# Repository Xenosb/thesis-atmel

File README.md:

# thesis-atmel

## Libraries
Some of the symbols and footprints are from KiCad Library
```https://github.com/KiCad/kicad-library```

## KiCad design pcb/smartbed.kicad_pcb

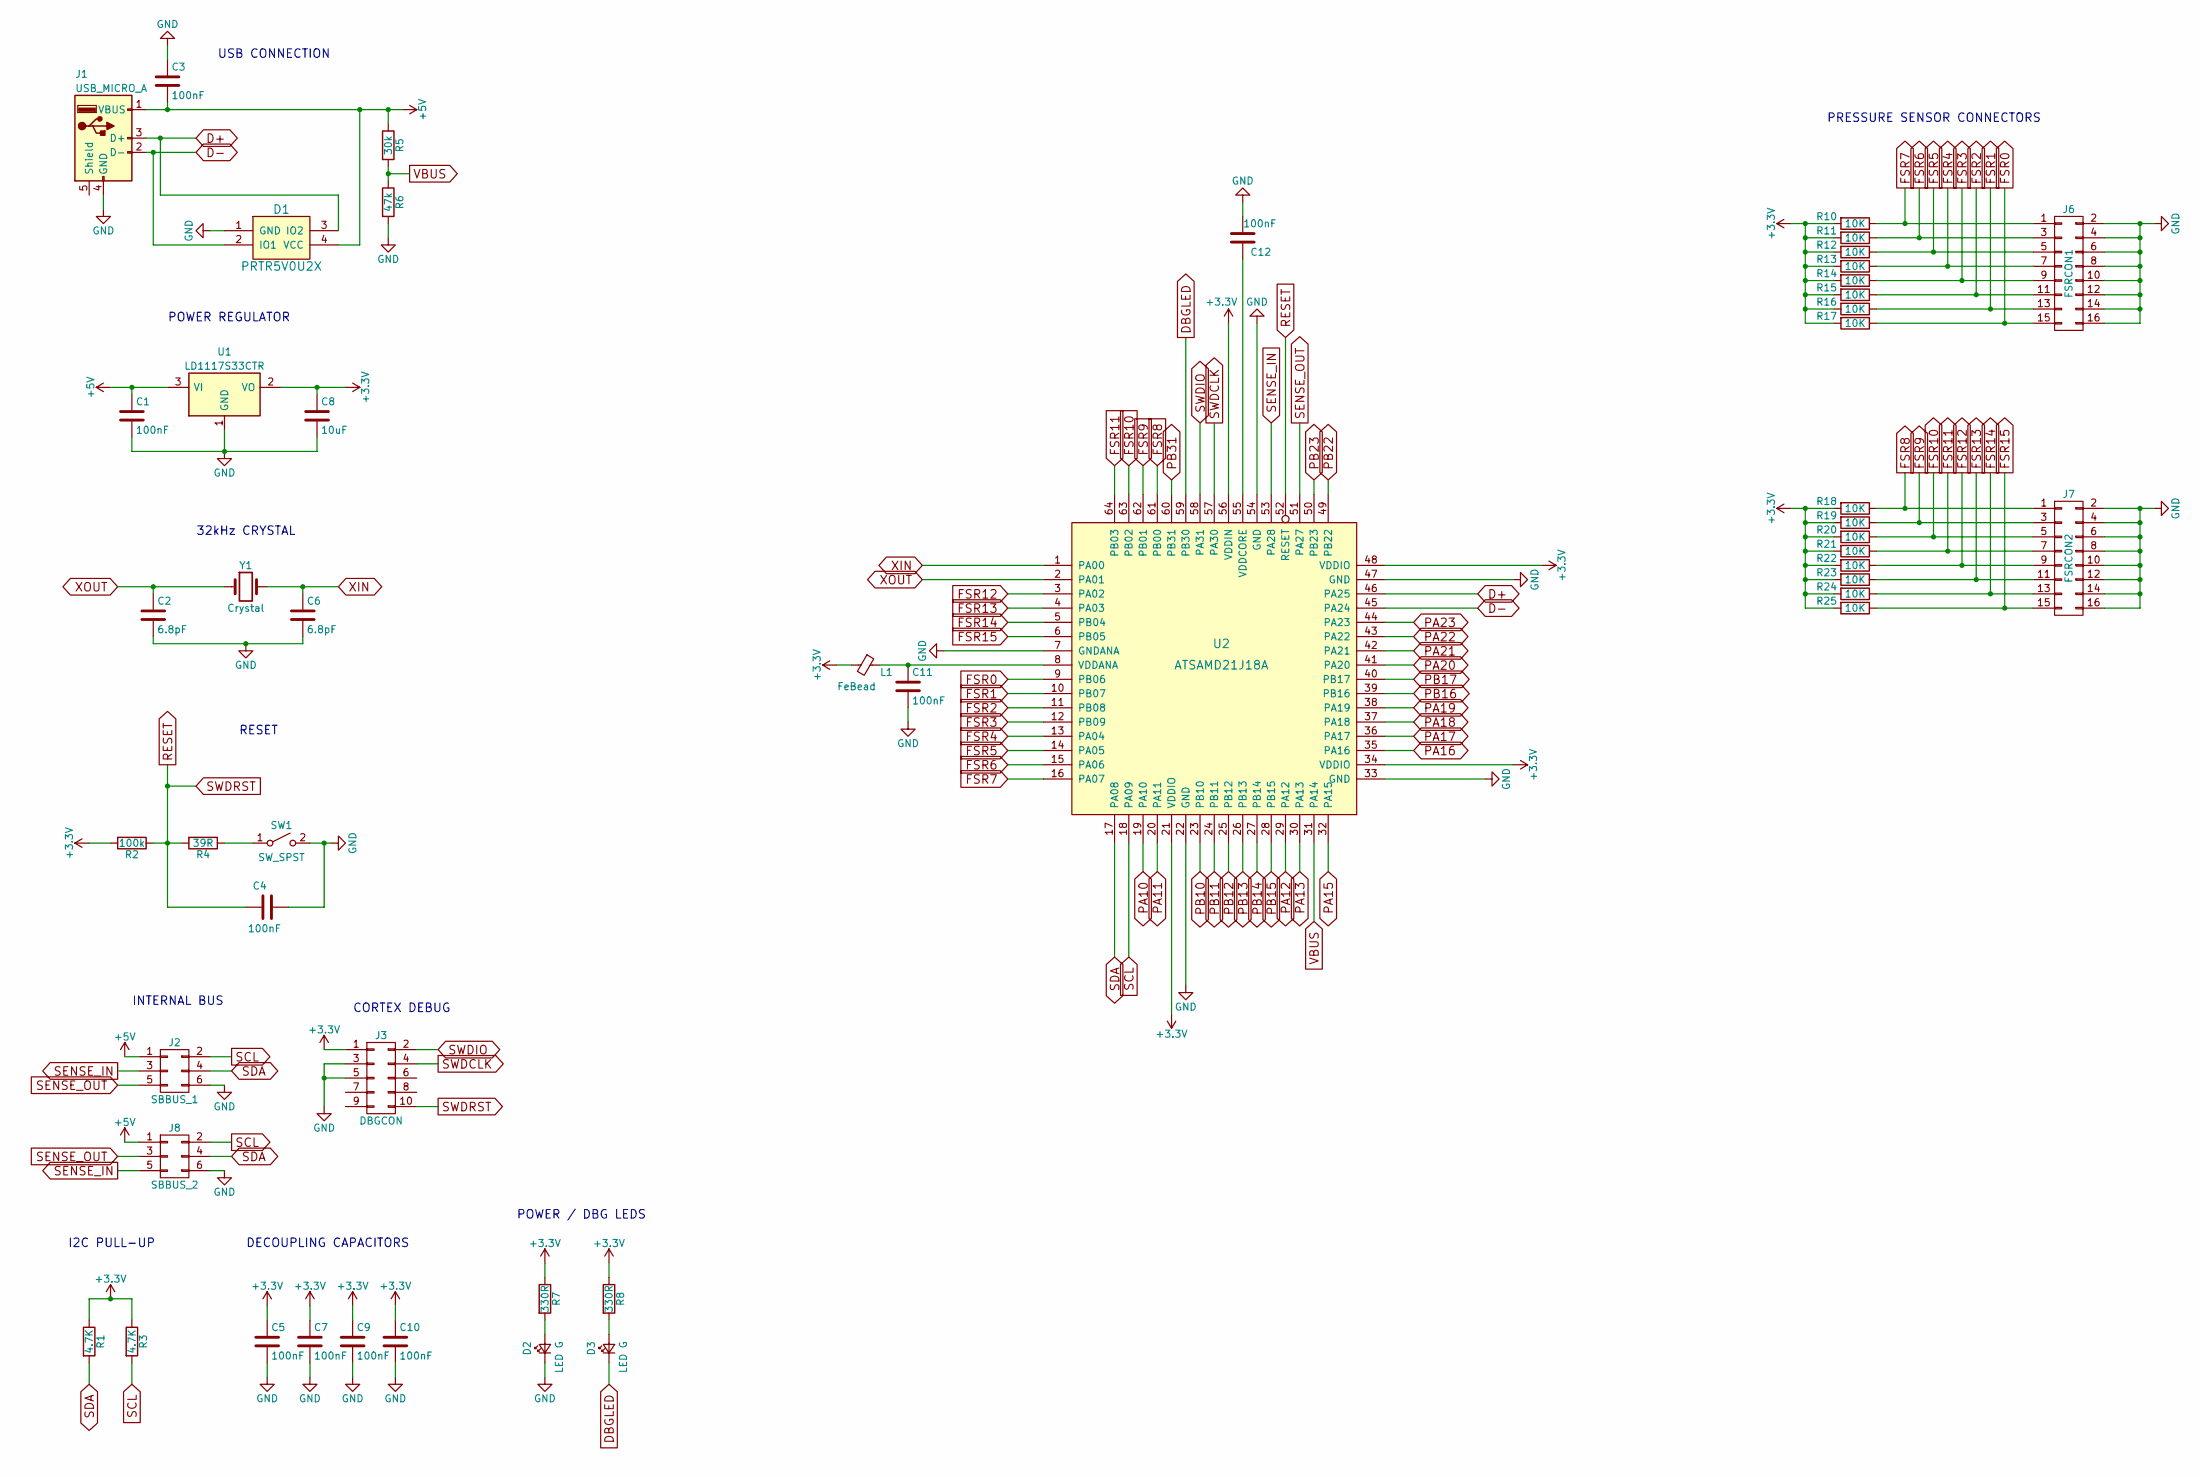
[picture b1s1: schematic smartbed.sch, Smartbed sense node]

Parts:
C1, C3, C4, C5, C7, C9, C10, C11, C12: 100nF; C_0603_HandSoldering
C2, C6: 6.8pF; C_0603_HandSoldering
C8: 10uF; C_0603_HandSoldering
D1: PRTR5V0U2X; SOT-143_Handsoldering
D2, D3: LED G; LED_0805
J1: USB_MICRO_A; USB_Micro-B
J2: SBBUS_1; IDC_Header_Straight_6pins
J3: DBGCON; IDC_Header_Straight_10pins
J6: FSRCON1; Pin_Header_Angled_2x08_Pitch2.54mm
J7: FSRCON2; Pin_Header_Angled_2x08_Pitch2.54mm
J8: SBBUS_2; IDC_Header_Straight_6pins
L1: FeBead; L_0603_HandSoldering
R1, R3: 4.7K; R_0805_HandSoldering
R2: 100k; R_0805_HandSoldering
R4: 39R; R_0805_HandSoldering
R5: 30k; R_0805_HandSoldering
R6: 47k; R_0805_HandSoldering
R7, R8: 330R; R_0805_HandSoldering
R10, R11, R12, R13, R14, R15, R16, R17, R18, R19, R20, R21, R22, R23, R24, R25: 10K; R_0805_HandSoldering
SW1: SW_SPST; SW_SPST_B3SL-1002P
U1: LD1117S33CTR; SOT-223
U2: ATSAMD21J18A; TQFP-64_10x10mm_Pitch0.5mm
Y1: Crystal; Crystal_Round_d3.0mm_Vertical

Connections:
+3V3: C5.1, C7.1, C8.1, C9.1, C10.1, J3.1, L1.2, R1.1, R2.2, R3.1, R7.1, R8.1, R10.2, R11.2, R12.2, R13.2, R14.2, R15.2, R16.2, R17.2, R18.2, R19.2, R20.2, R21.2, R22.2, R23.2, R24.2, R25.2, U1.2 (VO), U2.21 (VDDIO), U2.34 (VDDIO), U2.48 (VDDIO), U2.56 (VDDIN)
+5V: C1.1, C3.2, D1.4 (VCC), J1.1 (VBUS), J2.1, J8.1, R5.1, U1.3 (VI)
D+: D1.3 (IO2), J1.3 (D+), U2.46 (PA25)
D-: D1.2 (IO1), J1.2 (D-), U2.45 (PA24)
DBGLED: D3.1 (K), U2.59 (PB30)
FSR0: J6.15, R17.1, U2.9 (PB06)
FSR1: J6.13, R16.1, U2.10 (PB07)
FSR2: J6.11, R15.1, U2.11 (PB08)
FSR3: J6.9, R14.1, U2.12 (PB09)
FSR4: J6.7, R13.1, U2.13 (PA04)
FSR5: J6.5, R12.1, U2.14 (PA05)
FSR6: J6.3, R11.1, U2.15 (PA06)
FSR7: J6.1, R10.1, U2.16 (PA07)
FSR8: J7.1, R18.1, U2.61 (PB00)
FSR9: J7.3, R19.1, U2.62 (PB01)
FSR10: J7.5, R20.1, U2.63 (PB02)
FSR11: J7.7, R21.1, U2.64 (PB03)
FSR12: J7.9, R22.1, U2.3 (PA02)
FSR13: J7.11, R23.1, U2.4 (PA03)
FSR14: J7.13, R24.1, U2.5 (PB04)
FSR15: J7.15, R25.1, U2.6 (PB05)
GND: C1.2, C2.2, C3.1, C4.2, C5.2, C6.2, C7.2, C8.2, C9.2, C10.2, C11.2, C12.1, D1.1 (GND), D2.1 (K), J1.4 (GND), J2.6, J3.3, J3.5, J6.2, J6.4, J6.6, J6.8, J6.10, J6.12, J6.14, J6.16, J7.2, J7.4, J7.6, J7.8, J7.10, J7.12, J7.14, J7.16, J8.6, R6.2, SW1.2 (B), U1.1 (GND), U2.7 (GNDANA), U2.22 (GND), U2.33 (GND), U2.47 (GND), U2.54 (GND)
unnamed: C11.1, L1.1, U2.8 (VDDANA)
unnamed: C12.2, U2.55 (VDDCORE)
unnamed: D2.2 (A), R7.2
unnamed: D3.2 (A), R8.2
unnamed: R4.1, SW1.1 (A)
PA10: U2.19 (PA10)
PA11: U2.20 (PA11)
PA12: U2.29 (PA12)
PA13: U2.30 (PA13)
PA15: U2.32 (PA15)
PA16: U2.35 (PA16)
PA17: U2.36 (PA17)
PA18: U2.37 (PA18)
PA19: U2.38 (PA19)
PA20: U2.41 (PA20)
PA21: U2.42 (PA21)
PA22: U2.43 (PA22)
PA23: U2.44 (PA23)
PB10: U2.23 (PB10)
PB11: U2.24 (PB11)
PB12: U2.25 (PB12)
PB13: U2.26 (PB13)
PB14: U2.27 (PB14)
PB15: U2.28 (PB15)
PB16: U2.39 (PB16)
PB17: U2.40 (PB17)
PB22: U2.49 (PB22)
PB23: U2.50 (PB23)
PB31: U2.60 (PB31)
RESET: C4.1, J3.10, R2.1, R4.2, U2.52 (RESET)
SCL: J2.2, J8.2, R3.2, U2.18 (PA09)
SDA: J2.4, J8.4, R1.2, U2.17 (PA08)
SENSE_IN: J2.3, J8.5, U2.53 (PA28)
SENSE_OUT: J2.5, J8.3, U2.51 (PA27)
SWDCLK: J3.4, U2.57 (PA30)
SWDIO: J3.2, U2.58 (PA31)
VBUS: R5.2, R6.1, U2.31 (PA14)
XIN: C6.1, U2.1 (PA00), Y1.2
XOUT: C2.1, U2.2 (PA01), Y1.1

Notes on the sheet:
USB CONNECTION
INTERNAL BUS
POWER REGULATOR
32kHz CRYSTAL
RESET
I2C PULL-UP
CORTEX DEBUG
DECOUPLING CAPACITORS
POWER / DBG LEDS
PRESSURE SENSOR CONNECTORS

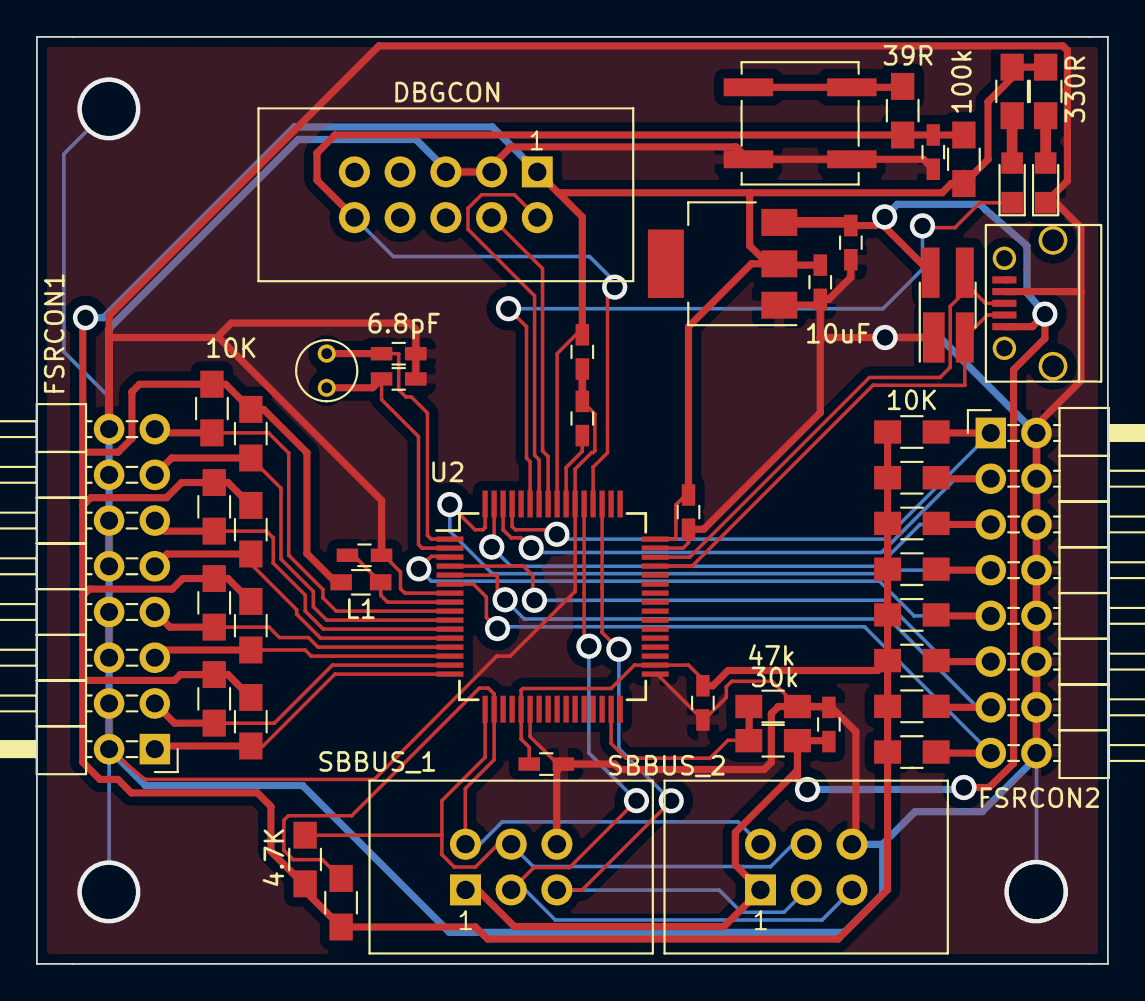
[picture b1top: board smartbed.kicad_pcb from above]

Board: 2 copper layers, 59.5 x 51.5 mm, 50 parts (0 on the bottom side), 37 nets.

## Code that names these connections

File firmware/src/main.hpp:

#define HW_VER 1
#define SW_VER 1

#include "mbed.h"
#include "Smartbed.hpp"

#define I2C_FREQ 100000
#define MAX_I2C_DATA_SIZE 100

#define EDISON_ADR 0x0a
#define NODE_ADR 0x10

#define I2C_SDA_PIN PA08
#define I2C_SCL_PIN PA09
#define LED_PIN PB30
#define SENSE_IN_PIN PA28
#define SENSE_OUT_PIN PA27

#define SENSOR_NUMBER 16

I2C_RESULT i2c_slave_worker(I2CSlave slave);
void process_i2c_call(I2C_RESULT i2c_data);
void process_read(I2C_RESULT i2c_data);
void process_write(I2C_RESULT i2c_data);
void process_broadcast(I2C_RESULT i2c_data);
void update_all_sensors();
int main();

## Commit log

2017-06-08 New gitiginre
2017-06-08 Added SAMD21 to library
2017-06-09 Added power supply, USB, internal bus
2017-06-09 Added I2C pull ups, reset button, xtal
2017-06-11 Added debug connector and capacitors
2017-06-11 Added FSR connectors
2017-06-11 Assigned footprints, started PCB
2017-06-12 Biggest part of board done
2017-06-12 Connected most of the traces
2017-06-13 Routed the board
2017-06-13 Revision 1
2017-06-13 Revision 2
2017-06-13 Edit board references
2017-06-13 Add ground planes
2017-06-14 Updated design to conform HTWG rules
2017-06-14 Fixed minor gitignore issue
2017-06-14 Minor PCB changes
2017-06-22 Minor changes to PCB, added HTML BOM
2017-07-07 Added platformio mbed project with readme
2017-07-07 Updated image URLs in readme
2017-07-07 Fixed mapping
2017-07-08 Added debug script, a bit of testing
2017-07-08 Added upload script and working i2c implementation
2017-07-08 Fixed i2c broadcast address
2017-07-09 Added I2C result class
2017-07-09 Organized i2c read, write and broadcast functions
2017-07-09 Added read and broadcaste i2c functions, added sense pins
2017-07-09 i2c address change and sense out write tested working
2017-07-10 Reading single sensor works
2017-07-11 All sensor data request added
2017-08-03 Minor gitignore change
2017-08-28 Fixed wierd issue with node sending only 1 byte over I2C when sensor was read
